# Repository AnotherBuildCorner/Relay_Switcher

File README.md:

# Relay_Switcher
DIY Relay bypass switcher for audio applications

Are you a Guitarist/Bassist?  Do you have a pedalboard that just keeps on getting more complicated?

Worried about losing the high end to the long capactive runs and buffers?

Or maybe you want the ability to control your Star-Trek level board from a small controller on your desk?

Or maybe you looked at the avaliable products, and practically fell out of your chair with the price tag?

Then look no further! In this project you'll find a modular capable, mono or stereo loop bypass switcher with wireless control capability.

## Notes:
V3 Jackless Is up and running in the same 6 back stacked form factor as V2. At this point I believe this represents the final version for this current system based on the WROOM32E. Why?
- After designing this board, I became aware of smaller form factor ESP32's such as the XIAO C6 platform, which is roughly the size of a US Quarter, and has enough GPIO pins to support at least 6 relays.
- These smaller implementations also appear to handle the mesh network past 4 nodes. In the past, while possible, implementing past 4 nodes required additional edits deep in the IDE that I was unable to implement at the time.
- With these smaller nodes, I may be able to use one C6 to control a 6 to 8 loop package box. Incorporated directly into the loop box. Meaning the only wires needed will be Power, and audio. No more RJ45 signal control wire.
- Further, with the practical limitiations of how many nodes are available lifted. The use of C6 nodes means the modularity is further improved to the point of having a control box behind the amp for example, in an effects loop configuration, and one or two on the main pedalboard.  Or even separate pedalboards for different uses.  Or different layers of a rack. The possibilites are endless.
- With a couple small onboard changes, power may even be supplied by the onboard USB connector. Which on it's face doesn't seem that helpful in a 9V power dominated space. However, commercial 5V to 9V power adapters are readily available, which means an entire system could be run from USB power, and by extension, the widely available USB power packs on the market. Why Boost the voltage, just to regulate back to 5V when the supply can be run on pure 5V?

V2 Jackless is up and running in a 6 bay stacked model. In the process a handful of lessons were picked up.
- One, for the jackless model a V3 utilizing probably 3 loops on a single panel with built in signal traces, and possibly breakaway functionality is likely. Attempting to wire the board interconnects resulted in a bit of a mess, one I'm not entirely happy with.
- Two, The original implementations use a completely separate power/control and signal path, not even the grounds are linked. This appears to be an error, and a future revision may include a solderable ground linking pad. In testing this linkage reduced the noise to virtually 0
- Three, the breakout board, while universal has a quirk. When used with the current V2 coms board, Power and ground on the 8 pins are not next to one another. Careful: This may fry some boards.
- Four, some of the pins used on the ESP-32 were linked to serial output, so when those pins are active, the serial monitor and control are disabled. 
## PCB's
### Main Driver Board
### V3
The V3 Design implements some of the noted design problems from V2. Development has continued exclusively with the 3.5mm pitch model. As these are the parts I have on hand. and increasing the terminal block size appears to have little practical benefit.

 Instead of utilizing individual loop boards, there are now a pair of boards linked by a ribbon cable. As a set, these combined boards can support either 6 mono/stereo loops, or 5 mono/stero loops and a mono input selector depending on relay configuration.

 Input Board

 Output Board

This change produces a couple of benefits. First is wiring is vastly improved. with the total wire soldering point count down from 7 per board ( L/R in, L/R out, Ground 9V, and Control signal.) Times 6 loop packages, for a total of 42 solder points. To 16 solder points total for the entire package. As well as being inline, ideal for a ribbon cable, as opposed to scattered across the board.

Additionally, the number of Voltage regulators is down from one per package, to one per PCB (with 3 loops on each). so a 66% reduction overall.

The mentioned power and signal ground linking has been added, provided by the G_link pads located on each PCB, in practice using booth may create a ground loop, so ideally soldering just one is reccomended.

Now the one loss from such a design (albeit minimal in practical usage) is the loops can no longer be order changed by moving around connectors inside the package (or perhaps in the future a complex multi relay network).  In practice this just means physically changing the order of the connected devices at the device instead, and is a minimal downside.

Both Boards Populated

Complete Stacked model Assembly

### V2

V2 makes some significant improvements over the V1 design. And introduces a second design.
the changes are as follows
- Length of board reduced to 61mm Long
- Reduced count of 2n7000 MOSFET drivers from 3 to 1
- Tied status LED directly to the control output for a net -1 2n7000
- Tied the two relay coils together, controlled by single 2n7000

  Among the boards are now the standard stereo jack model, and a pair of new "jackless" models
  The jackless models utilize either a 4x3.5mm pitch or 4x5mm pitch screw terminal block on the IO. this reduces the cost per loop by up $10 in full implementation
  Additionally, it appears the space consumption overall will be significantly reduced with the new design

  The reduced board size should enable either the w/ jack or jackless versions to fit inside a standard 1032L Aluminium looper case
  In testing, the relay coils consume 30mA each, well under the 2n7000's maximum 200mA current.
  the new status LED position can also function as a pulldown for the inputs, reduces the 2n7000 count. And the originals had some current leakage which caused the led to be partially illuminated all the time

### V1

Pictured above is the main relay board. The core Arcitecture is one 5V coil DPDT Relay per signal channel. So for stereo configurations, two relays are required.
Each Relay is driven by a MOSFET 2n7000 switch circuit. As well as the status LED. All three MOSFET gates are tied to a common signal pin, and configured for 3.3V logic.

Each board is also equipped with a 74L05 5V regulator to drop the incoming 9V power, and provide supply for the relay switching.

Each board also has dual power connectors, as well as 3 pin 2.54mm spaced pins for the signal  this alows for easy connections between multiple boards in series.

Finally, the boards are set up to accept switched 1/4 inch stereo jacks. With the switches internally connected, so loops without connections pass signal in either active or inactive state.

(Add PCB wire photos here)

Of further note, was the consideration to keep audio, and control/ power wires as far away, and with minimal crossing as possible. This is to reduce crosstalk from the processor and power supplies into the audio path.

Future iterations will focus on compressing the PCB into a space suitable for a 16L Aluminium looper enclosure. Or possibly a design set up to directly connect to the mono/stereo signal wires, therby reducing the need for the 1/4 Barrel connectors, and reducing the required 1/4 Plugs by 1/2.  This also helps with space considerations.  Considering these plugs cost upwards of $4 each, cutting in half is most welcome, although this reduces how universal this device will be.

### Processor Board
### V2

Changes from V1 to V2 are a different footprint ESP32.  now the Wroom 32E is the standard, with 38 pins avaiable.
The individual pin headers have been replaced by 3x rj45 connectors. each is configured with 6 individual GPIO pins, as well as a 9V connection, and ground.
Additionally, a new breakout board for the rj45 on the receiver end has been created.

### V1

The microprocessor controlling the relays is an ESP32 Devkit C V3 Chosen for it's relative availability, low price, access to Arduino IDE code, and most importantly the dedicated ESP_NOW wireless communication protocol, which will be used to communicate between boards.
This is a relatively simple IO board for connecting to the GPIO of the processor board. The only extra element is another 74L05 voltage regulator connected to the 5V input of the dev board and the 4 pullup resistors slotted in on GPIO pins which only provide input (not suitable for the relay control, but there are already plenty of pins available for most applications).

One shortcoming, there may not be enough GPIO pins to handle the control switches, status LED's, screen, and rotary encoder(s). But this is all currently under development.

This version has a single easily remedied flaw. I had to create a footprint for the ESP32 used as they were what I had to hand, but appear to no longer be made. Well I flipped a ground and power connection, shorting 3.3V power to ground. For now it's just a matter of cutting the trace.

Future versions will probably switch to using a V4 devkit, or the newer devkits based on the S3 processor for more GPIO, and to retain more current availability. 

### IO Board
### V2

The new V2 board corrects an error in the input switching, resulting in one of the inputs being completely unusable.
Additionally, the board size has been significantly reduced in length. and the IO board direct pinouts have been moved directly under each jack.

### V1

This is very similar to the main relay boards.
The differences are the use of the single relay, the dual LED indicators, and the large electrolytic capacitor on the 9V rail.
The Capacitor is a filtering cap, as most of the 9V power supplies will be switched mode supplies, and noise prone.
The relay is no longer used to enable/disable a loop. but instead is used to switch between two possible inputs/outputs. With the other half of the relay dedicated to controlling the indicator LED's
lastly there are direct pinouts on the back of each 1/4 Barrel connector. Should switching features not be desired, these can be used to link the relay loops directly to an output without extra parts.

## Housings
### Control Housing 

### Relay housing V2 
JAckless model.

The latest relay switch is setup to accept 5 of the jackless relay boards, and one V2 IO board with the RJ45 connection board in front.  however this new model is half the height of V1, and is stackable. By splitting the units into modules of 5, this enables break points for things such as Volume pedals, and always on boosts between loop modules. Additional smaller size stackable modules will likely be produced in the future. No one single module can exceed more than 6 relay modules due to the RJ45 connection's configuration.

### Relay housing V1
(picure)
The current housing design uses horizontally stacked relay loops, with a total count of 10. Plus the input and output boards. The IO is located on the front for accesibility, with the loops located on the back.

### Control Housing
(picture
The current design is a single print, 6 switch control with provisions to add a 128X64 OLED.
At present this is in it's early stages, so no provisions to mount the control board, or a larger screen have been included. This will come around in V2  The footswitches are spaced to allow foot, or hand use currently. And the board can be purely powered from a 5V usb supply though the ESP32 board.

## Code
(Coming Soon...)

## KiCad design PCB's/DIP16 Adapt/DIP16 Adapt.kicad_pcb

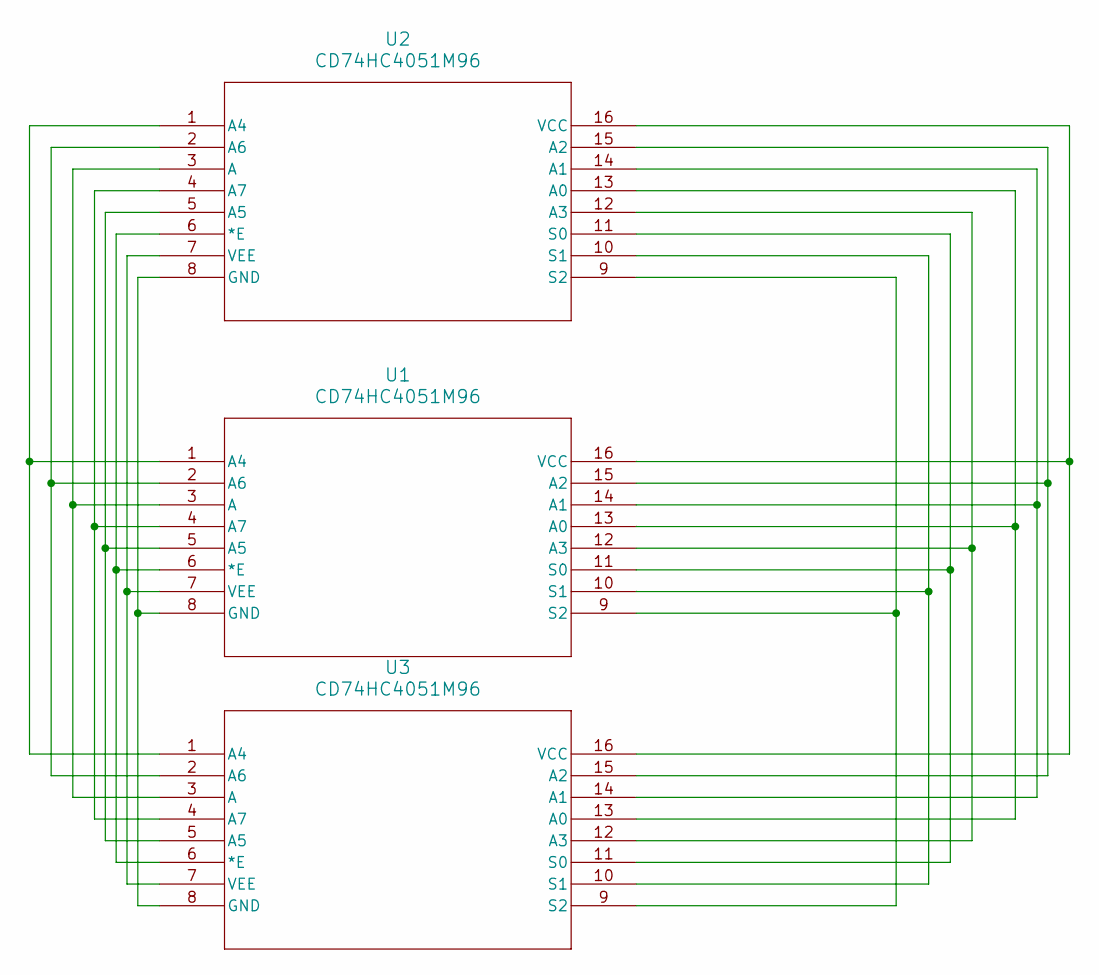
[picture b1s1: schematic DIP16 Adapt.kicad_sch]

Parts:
U1: CD74HC4051M96; DIP-16_W7.62mm_LongPads
U2: CD74HC4051M96; D16
U3: CD74HC4051M96; PW16

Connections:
unnamed: U1.6 (*E), U2.6 (*E), U3.6 (*E)
unnamed: U1.13 (A0), U2.13 (A0), U3.13 (A0)
unnamed: U1.14 (A1), U2.14 (A1), U3.14 (A1)
unnamed: U1.15 (A2), U2.15 (A2), U3.15 (A2)
unnamed: U1.12 (A3), U2.12 (A3), U3.12 (A3)
unnamed: U1.1 (A4), U2.1 (A4), U3.1 (A4)
unnamed: U1.5 (A5), U2.5 (A5), U3.5 (A5)
unnamed: U1.2 (A6), U2.2 (A6), U3.2 (A6)
unnamed: U1.4 (A7), U2.4 (A7), U3.4 (A7)
unnamed: U1.3 (A), U2.3 (A), U3.3 (A)
unnamed: U1.8 (GND), U2.8 (GND), U3.8 (GND)
unnamed: U1.11 (S0), U2.11 (S0), U3.11 (S0)
unnamed: U1.10 (S1), U2.10 (S1), U3.10 (S1)
unnamed: U1.9 (S2), U2.9 (S2), U3.9 (S2)
unnamed: U1.16 (VCC), U2.16 (VCC), U3.16 (VCC)
unnamed: U1.7 (VEE), U2.7 (VEE), U3.7 (VEE)

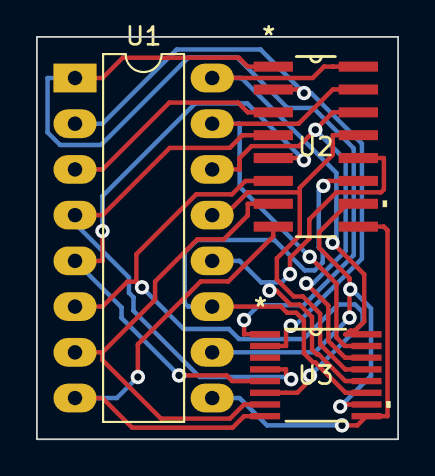
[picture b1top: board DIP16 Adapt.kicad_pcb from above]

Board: 2 copper layers, 20.1 x 22.4 mm, 3 parts (0 on the bottom side), 16 nets.

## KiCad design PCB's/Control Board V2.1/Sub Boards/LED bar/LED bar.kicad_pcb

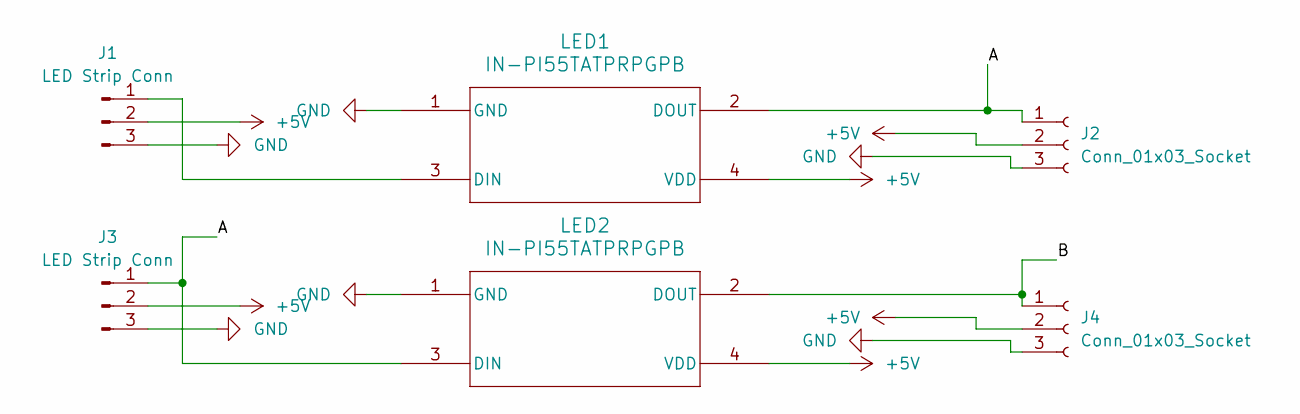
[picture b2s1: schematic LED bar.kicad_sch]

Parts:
J1, J3: LED Strip Conn; PinHeader_1x03_P2.54mm_Vertical
J2, J4: Conn_01x03_Socket; PinHeader_1x03_P2.54mm_Vertical
LED1, LED2: IN-PI55TATPRPGPB; LED_IN-PI55TAT_INL

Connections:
+5V: J1.2, J2.2, J3.2, J4.2, LED1.4 (VDD), LED2.4 (VDD)
/A: J2.1, J3.1, LED1.2 (DOUT), LED2.3 (DIN)
/B: J4.1, LED2.2 (DOUT)
GND: J1.3, J2.3, J3.3, J4.3, LED1.1 (GND), LED2.1 (GND)
unnamed: J1.1, LED1.3 (DIN)

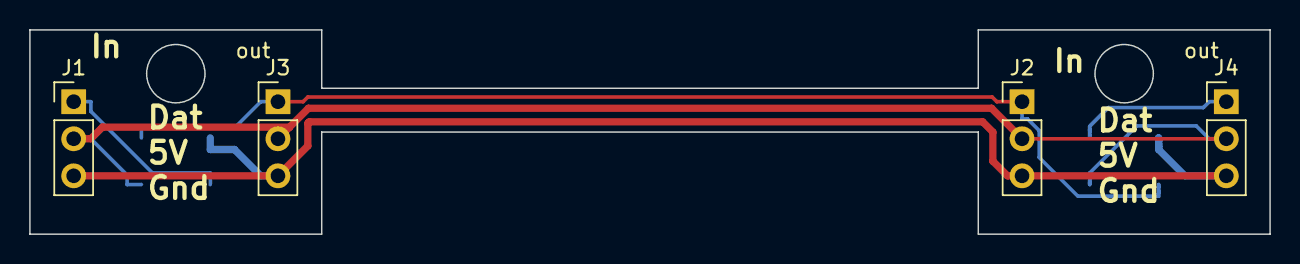
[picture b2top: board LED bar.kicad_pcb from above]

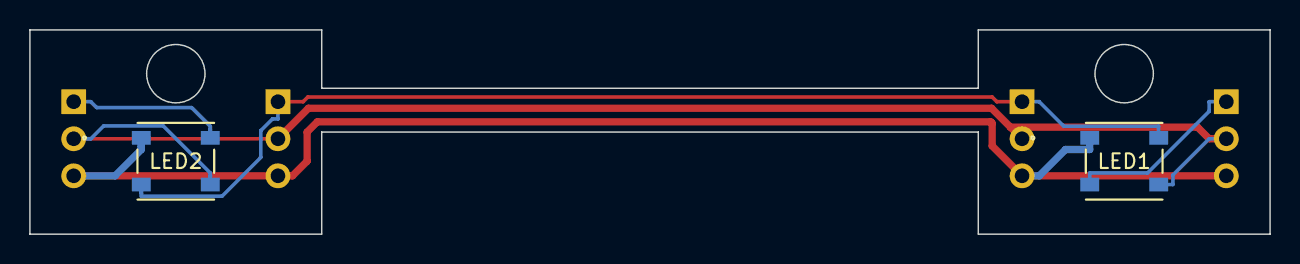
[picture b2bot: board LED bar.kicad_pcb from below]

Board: 2 copper layers, 85.0 x 14.0 mm, 6 parts (2 on the bottom side), 5 nets.

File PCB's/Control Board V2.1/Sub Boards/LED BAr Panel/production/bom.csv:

Designator,Footprint,Quantity,Value,LCSC Part #
"J1_5, J1_4, J1_3, J1_2, J1, J3_5, J3_4, J3_3, J3_2, J3",PinHeader_1x03_P2.54mm_Vertical,10,LED Strip Conn,
"J2_5, J2_4, J2_3, J2_2, J2, J4_5, J4_4, J4_3, J4_2, J4",PinHeader_1x03_P2.54mm_Vertical,10,Conn_01x03_Socket,
"KiKit_MB_10_1, KiKit_MB_10_2, KiKit_MB_10_3, KiKit_MB_10_4, KiKit_MB_11_1, KiKit_MB_11_2, KiKit_MB_11_3, KiKit_MB_11_4, KiKit_MB_12_1, KiKit_MB_12_2, KiKit_MB_12_3, KiKit_MB_12_4, KiKit_MB_13_1, KiKit_MB_13_2, KiKit_MB_13_3, KiKit_MB_13_4, KiKit_MB_14_1, KiKit_MB_14_2, KiKit_MB_14_3, KiKit_MB_14_4, KiKit_MB_15_1, KiKit_MB_15_2, KiKit_MB_15_3, KiKit_MB_15_4, KiKit_MB_16_1, KiKit_MB_16_2, KiKit_MB_16_3, KiKit_MB_16_4, KiKit_MB_17_1, KiKit_MB_17_2, KiKit_MB_17_3, KiKit_MB_17_4, KiKit_MB_18_1, KiKit_MB_18_2, KiKit_MB_18_3, KiKit_MB_18_4, KiKit_MB_19_1, KiKit_MB_19_2, KiKit_MB_19_3, KiKit_MB_19_4, KiKit_MB_1_1, KiKit_MB_1_2, KiKit_MB_1_3, KiKit_MB_1_4, KiKit_MB_20_1, KiKit_MB_20_2, KiKit_MB_20_3, KiKit_MB_20_4, KiKit_MB_21_1, KiKit_MB_21_2, KiKit_MB_21_3, KiKit_MB_21_4, KiKit_MB_22_1, KiKit_MB_22_2, KiKit_MB_22_3, KiKit_MB_22_4, KiKit_MB_23_1, KiKit_MB_23_2, KiKit_MB_23_3, KiKit_MB_23_4, KiKit_MB_24_1, KiKit_MB_24_2, KiKit_MB_24_3, KiKit_MB_24_4, KiKit_MB_25_1, KiKit_MB_25_2, KiKit_MB_25_3, KiKit_MB_25_4, KiKit_MB_26_1, KiKit_MB_26_2, KiKit_MB_26_3, KiKit_MB_26_4, KiKit_MB_27_1, KiKit_MB_27_2, KiKit_MB_27_3, KiKit_MB_27_4, KiKit_MB_28_1, KiKit_MB_28_2, KiKit_MB_28_3, KiKit_MB_28_4, KiKit_MB_29_1, KiKit_MB_29_2, KiKit_MB_29_3, KiKit_MB_29_4, KiKit_MB_2_1, KiKit_MB_2_2, KiKit_MB_2_3, KiKit_MB_2_4, KiKit_MB_30_1, KiKit_MB_30_2, KiKit_MB_30_3, KiKit_MB_30_4, KiKit_MB_31_1, KiKit_MB_31_2, KiKit_MB_31_3, KiKit_MB_31_4, KiKit_MB_32_1, KiKit_MB_32_2, KiKit_MB_32_3, KiKit_MB_32_4, KiKit_MB_33_1, KiKit_MB_33_2, KiKit_MB_33_3, KiKit_MB_33_4, KiKit_MB_34_1, KiKit_MB_34_2, KiKit_MB_34_3, KiKit_MB_34_4, KiKit_MB_35_1, KiKit_MB_35_2, KiKit_MB_35_3, KiKit_MB_35_4, KiKit_MB_36_1, KiKit_MB_36_2, KiKit_MB_36_3, KiKit_MB_36_4, KiKit_MB_37_1, KiKit_MB_37_2, KiKit_MB_37_3, KiKit_MB_37_4, KiKit_MB_38_1, KiKit_MB_38_2, KiKit_MB_38_3, KiKit_MB_38_4, KiKit_MB_39_1, KiKit_MB_39_2, KiKit_MB_39_3, KiKit_MB_39_4, KiKit_MB_3_1, KiKit_MB_3_2, KiKit_MB_3_3, KiKit_MB_3_4, KiKit_MB_40_1, KiKit_MB_40_2, KiKit_MB_40_3, KiKit_MB_40_4, KiKit_MB_41_1, KiKit_MB_41_2, KiKit_MB_41_3, KiKit_MB_41_4, KiKit_MB_42_1, KiKit_MB_42_2, KiKit_MB_42_3, KiKit_MB_42_4, KiKit_MB_43_1, KiKit_MB_43_2, KiKit_MB_43_3, KiKit_MB_43_4, KiKit_MB_44_1, KiKit_MB_44_2, KiKit_MB_44_3, KiKit_MB_44_4, KiKit_MB_45_1, KiKit_MB_45_2, KiKit_MB_45_3, KiKit_MB_45_4, KiKit_MB_46_1, KiKit_MB_46_2, KiKit_MB_46_3, KiKit_MB_46_4, KiKit_MB_47_1, KiKit_MB_47_2, KiKit_MB_47_3, KiKit_MB_47_4, KiKit_MB_48_1, KiKit_MB_48_2, KiKit_MB_48_3, KiKit_MB_48_4, KiKit_MB_4_1, KiKit_MB_4_2, KiKit_MB_4_3, KiKit_MB_4_4, KiKit_MB_5_1, KiKit_MB_5_2, KiKit_MB_5_3, KiKit_MB_5_4, KiKit_MB_6_1, KiKit_MB_6_2, KiKit_MB_6_3, KiKit_MB_6_4, KiKit_MB_7_1, KiKit_MB_7_2, KiKit_MB_7_3, KiKit_MB_7_4, KiKit_MB_8_1, KiKit_MB_8_2, KiKit_MB_8_3, KiKit_MB_8_4, KiKit_MB_9_1, KiKit_MB_9_2, KiKit_MB_9_3, KiKit_MB_9_4",NPTH,192,NPTH,
"LED1_5, LED1_4, LED1_3, LED1_2, LED1, LED2_5, LED2_4, LED2_3, LED2_2, LED2",LED_IN-PI55TAT_INL,10,IN-PI55TATPRPGPB,

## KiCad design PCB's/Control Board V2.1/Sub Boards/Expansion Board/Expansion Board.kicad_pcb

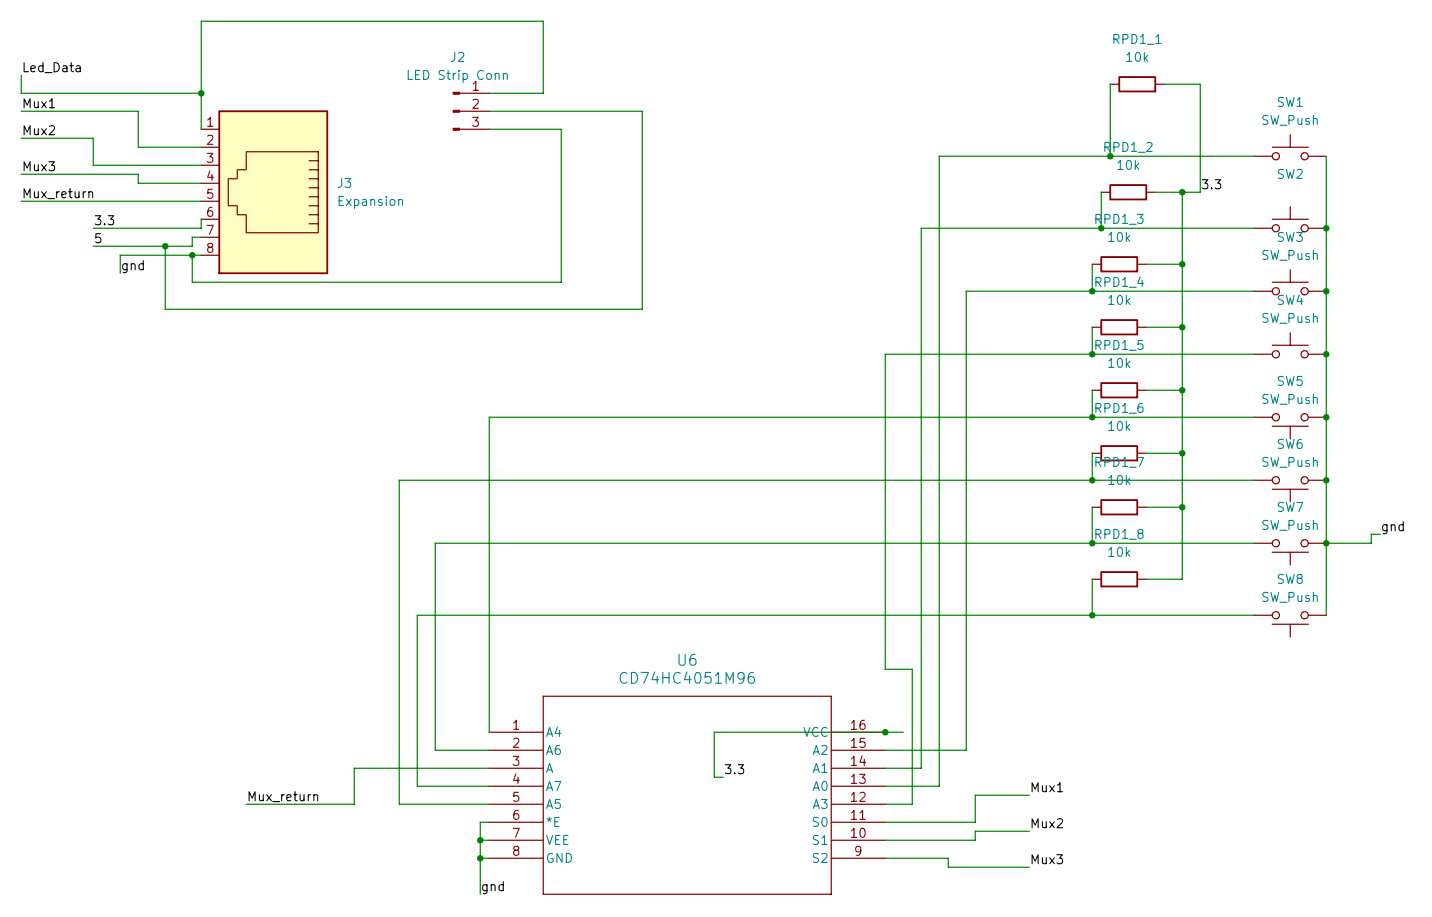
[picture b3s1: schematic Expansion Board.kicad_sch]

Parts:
J2: LED Strip Conn; PinHeader_1x03_P2.54mm_Vertical
J3: Expansion; RJ45_Amphenol_54602-x08_Horizontal
RPD1_1, RPD1_2, RPD1_3, RPD1_4, RPD1_5, RPD1_6, RPD1_7, RPD1_8: 10k; R_0805_2012Metric_Pad1.20x1.40mm_HandSolder
SW1, SW3, SW4, SW5, SW6, SW7, SW8: SW_Push; TerminalBlock_4Ucon_1x02_P3.50mm_Vertical
SW2: TerminalBlock_4Ucon_1x02_P3.50mm_Vertical
U6: CD74HC4051M96; QSOP-16_3.9x4.9mm_P0.635mm

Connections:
/3.3: J3.6, RPD1_1.2, RPD1_2.2, RPD1_3.2, RPD1_4.2, RPD1_5.2, RPD1_6.2, RPD1_7.2, RPD1_8.2, U6.16 (VCC)
/5: J2.2, J3.7
/Led_Data: J2.1, J3.1
/Mux1: J3.2, U6.11 (S0)
/Mux2: J3.3, U6.10 (S1)
/Mux3: J3.4, U6.9 (S2)
/Mux_return: J3.5, U6.3 (A)
/gnd: J2.3, J3.8, SW1.2, SW2.2, SW3.2, SW4.2, SW5.1, SW6.1, SW7.1, SW8.1, U6.6 (*E), U6.7 (VEE), U6.8 (GND)
unnamed: RPD1_1.1, SW1.1, U6.13 (A0)
unnamed: RPD1_2.1, SW2.1, U6.14 (A1)
unnamed: RPD1_3.1, SW3.1, U6.15 (A2)
unnamed: RPD1_4.1, SW4.1, U6.12 (A3)
unnamed: RPD1_5.1, SW5.2, U6.1 (A4)
unnamed: RPD1_6.1, SW6.2, U6.5 (A5)
unnamed: RPD1_7.1, SW7.2, U6.2 (A6)
unnamed: RPD1_8.1, SW8.2, U6.4 (A7)

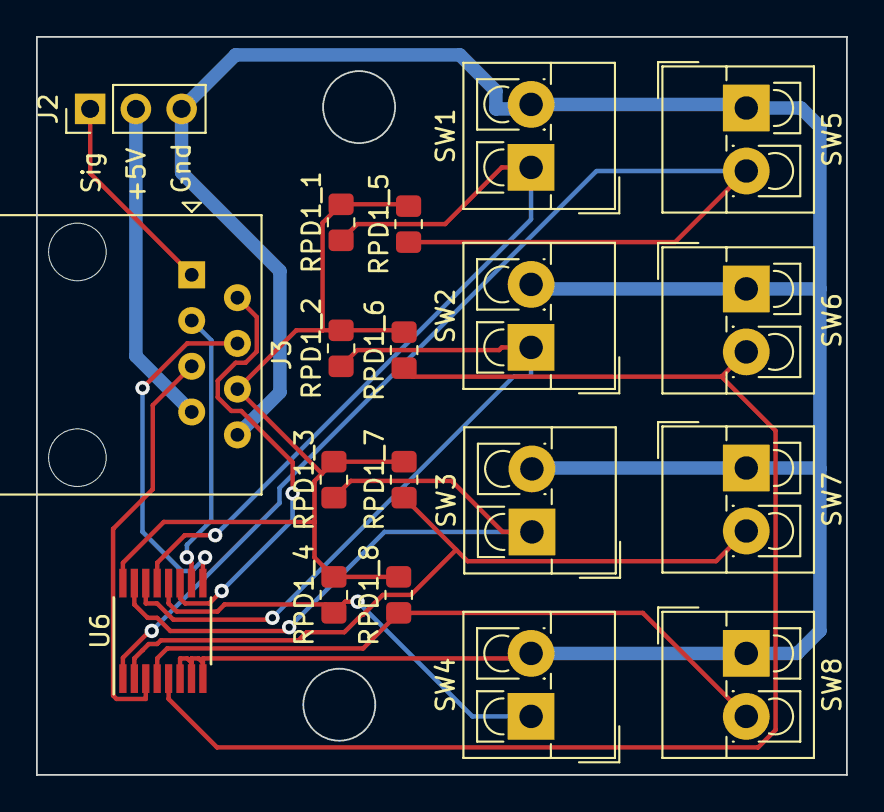
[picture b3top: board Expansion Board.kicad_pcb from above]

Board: 2 copper layers, 45.0 x 41.0 mm, 19 parts (0 on the bottom side), 16 nets.

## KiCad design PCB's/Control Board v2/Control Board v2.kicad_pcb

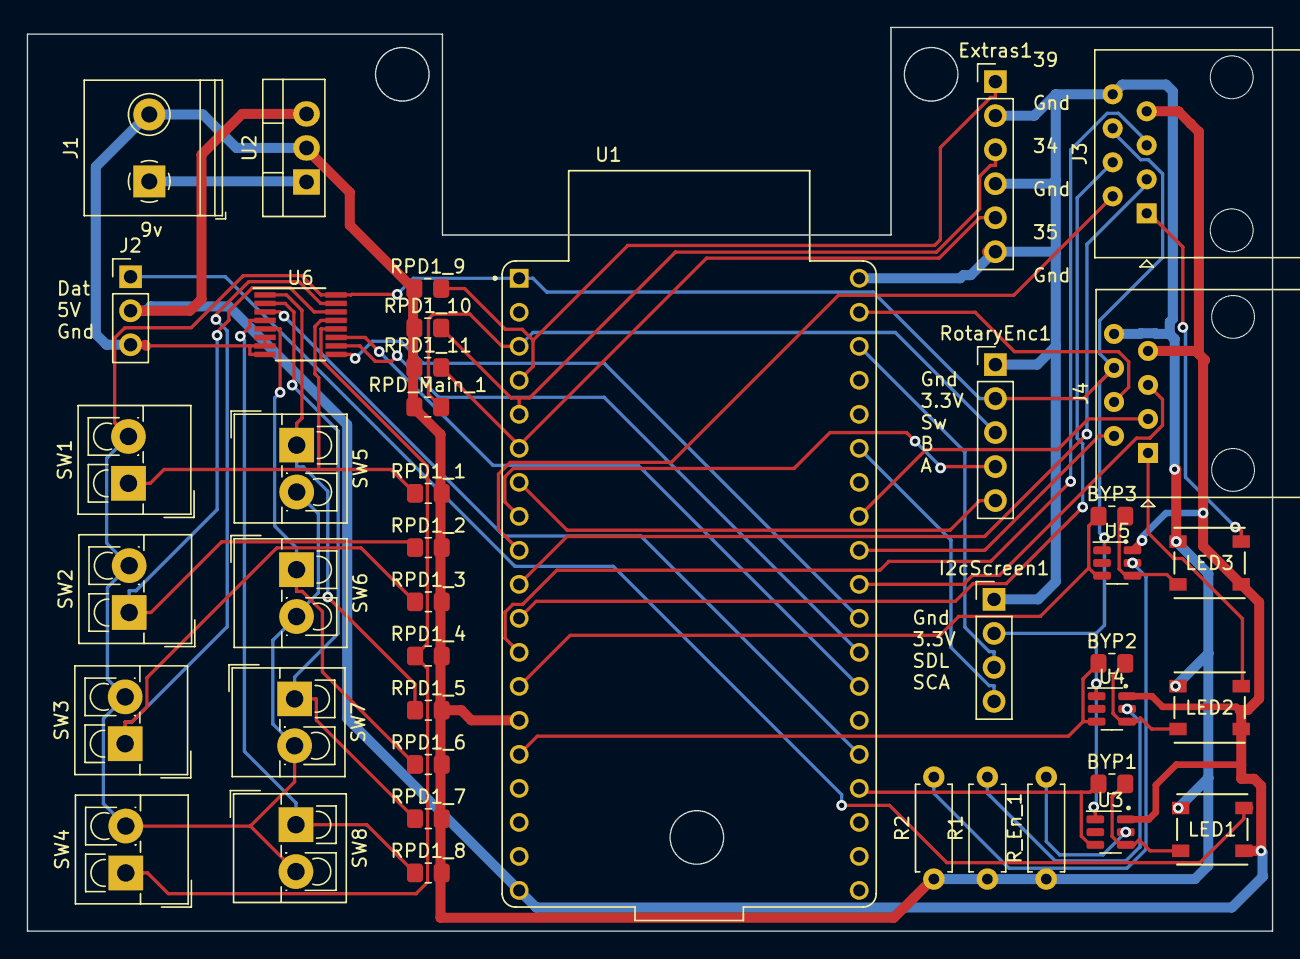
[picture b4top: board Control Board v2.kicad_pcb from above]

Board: 2 copper layers, 93.0 x 67.5 mm, 42 parts (0 on the bottom side), 44 nets.

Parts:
BYP1, BYP2, BYP3: R_0805_2012Metric_Pad1.20x1.40mm_HandSolder
Extras1: Conn_01x06_Pin; PinHeader_1x06_P2.54mm_Vertical
I2cScreen1: Conn_01x05_Pin; PinHeader_1x04_P2.54mm_Vertical
J1: Power In; TerminalBlock_Philmore_TB132_1x02_P5.00mm_Horizontal
J2: LED Strip Conn; PinHeader_1x03_P2.54mm_Vertical
J3, J4: Expansion; RJ45_Amphenol_54602-x08_Horizontal
LED1, LED2, LED3: IN-PI55TATPRPGPB; LED_IN-PI55TAT_INL
R1, R2: R; R_Axial_DIN0207_L6.3mm_D2.5mm_P7.62mm_Horizontal
RPD1_1, RPD1_2, RPD1_3, RPD1_4, RPD1_5, RPD1_6, RPD1_7, RPD1_8, RPD1_9, RPD1_10, RPD1_11: 10k; R_0805_2012Metric_Pad1.20x1.40mm_HandSolder
RPD_Main_1: 10k; R_0805_2012Metric_Pad1.20x1.40mm_HandSolder
R_En_1: R; R_Axial_DIN0207_L6.3mm_D2.5mm_P7.62mm_Horizontal
RotaryEnc1: Conn_01x05_Pin; PinHeader_1x05_P2.54mm_Vertical
SW1, SW2, SW3, SW4, SW5, SW6, SW7, SW8: SW_Push; TerminalBlock_4Ucon_1x02_P3.50mm_Vertical
U1: ESP32-DEVKITC-32E; MODULE_ESP32-DEVKITC-32E
U2: L7805; TO-220-3_Vertical
U3, U4, U5: TXS0101DBV; SOT-23-6
U6: CD74HC4051M96; QSOP-16_3.9x4.9mm_P0.635mm

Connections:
+3.3V: I2cScreen1.2, J3.6, J4.6, RotaryEnc1.2, SW1.2, SW2.2, SW3.2, SW4.2, SW5.2, SW6.2, SW7.2, SW8.2, U1.J2_1 (3V3), U3.1 (V_{CCA}), U4.1 (V_{CCA}), U5.1 (V_{CCA}), U6.16 (VCC)
+5V: J2.2, J3.7, J4.7, LED1.4 (VDD), LED2.4 (VDD), LED3.4 (VDD), U1.J2_19 (EXT_5V), U2.3 (OUT), U3.6 (V_{CCB}), U4.6 (V_{CCB}), U5.6 (V_{CCB})
+9V: J1.1, U2.1 (IN)
/Enc_A: RotaryEnc1.5, U1.J2_7 (IO32)
/Enc_B: RotaryEnc1.4, U1.J2_8 (IO33)
/Enc_Sw: RPD_Main_1.2, RotaryEnc1.3, U1.J2_3 (SENSOR_VP)
/GP34: Extras1.3, RPD1_10.2, U1.J2_5 (IO34)
/GP35: Extras1.5, RPD1_11.2, U1.J2_6 (IO35)
/GP39: Extras1.1, RPD1_9.2, U1.J2_4 (SENSOR_VN)
/I2C_SCL: I2cScreen1.3, U1.J3_3 (IO22)
/I2C_SDA: I2cScreen1.4, U1.J3_6 (IO21)
/Mux2_1: J4.2, U1.J3_9 (IO18)
/Mux2_2: J4.3, U1.J3_8 (IO19)
/Mux2_3: J4.4, U1.J3_2 (IO23)
/Mux2_return: J4.5, U1.J3_10 (IO5)
/Mux3_1: J3.2, U1.J2_9 (IO25)
/Mux3_2: J3.3, U1.J2_10 (IO26)
/Mux3_3: J3.4, U1.J2_11 (IO27)
/Mux3_return: J3.5, U1.J2_12 (IO14)
GND: Extras1.2, Extras1.4, Extras1.6, I2cScreen1.1, J1.2, J2.3, J3.8, J4.8, LED1.1 (GND), LED2.1 (GND), LED3.1 (GND), R1.1, R2.1, RPD1_1.2, RPD1_2.2, RPD1_3.2, RPD1_4.2, RPD1_5.2, RPD1_6.2, RPD1_7.2, RPD1_8.2, RPD1_9.1, RPD1_10.1, RPD1_11.1, RPD_Main_1.1, R_En_1.1, RotaryEnc1.1, U1.J2_14 (GND_J2_14), U1.J3_1 (GND_J3_1), U2.2 (GND), U6.6 (*E), U6.7 (VEE), U6.8 (GND)
LED_1_Data: J2.1, LED1.2 (DOUT)
LED_1_sig: BYP1.1, U1.J3_16 (IO15), U3.3 (A)
LED_2_Data: J4.1, LED2.2 (DOUT)
LED_2_sig: BYP2.1, U1.J2_15 (IO13), U4.3 (A)
LED_3_Data: J3.1, LED3.2 (DOUT)
LED_3_sig: BYP3.1, U1.J2_13 (IO12), U5.3 (A)
Mux1_1: U1.J3_13 (IO4), U6.11 (S0)
Mux1_2: U1.J3_12 (IO16), U6.10 (S1)
Mux1_3: U1.J3_11 (IO17), U6.9 (S2)
Mux1_return: U1.J3_15 (IO2), U6.3 (A)
unnamed: BYP1.2, LED1.3 (DIN), U3.4 (B)
unnamed: BYP2.2, LED2.3 (DIN), U4.4 (B)
unnamed: BYP3.2, LED3.3 (DIN), U5.4 (B)
unnamed: R_En_1.2, U3.5 (OE)
unnamed: R1.2, U4.5 (OE)
unnamed: R2.2, U5.5 (OE)
unnamed: RPD1_1.1, SW1.1, U6.13 (A0)
unnamed: RPD1_2.1, SW2.1, U6.14 (A1)
unnamed: RPD1_3.1, SW3.1, U6.15 (A2)
unnamed: RPD1_4.1, SW4.1, U6.12 (A3)
unnamed: RPD1_5.1, SW5.1, U6.1 (A4)
unnamed: RPD1_6.1, SW6.1, U6.5 (A5)
unnamed: RPD1_7.1, SW7.1, U6.2 (A6)
unnamed: RPD1_8.1, SW8.1, U6.4 (A7)

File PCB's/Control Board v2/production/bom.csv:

Designator,Footprint,Quantity,Value,LCSC Part #
"BYP1, BYP2, BYP3",0805,3,~,
Extras1,PinHeader_1x06_P2.54mm_Vertical,1,Conn_01x06_Pin,
I2cScreen1,PinHeader_1x04_P2.54mm_Vertical,1,Conn_01x05_Pin,
J1,TerminalBlock_Philmore_TB132_1x02_P5.00mm_Horizontal,1,Power In,
J2,PinHeader_1x03_P2.54mm_Vertical,1,LED Strip Conn,
"J3, J4",RJ45_Amphenol_54602-x08_Horizontal,2,Expansion,
"LED1, LED2, LED3",LED_IN-PI55TAT_INL,3,IN-PI55TATPRPGPB,
"R1, R2, R_En_1",R_Axial_DIN0207_L6.3mm_D2.5mm_P7.62mm_Horizontal,3,R,
"RPD1_1, RPD1_10, RPD1_11, RPD1_2, RPD1_3, RPD1_4, RPD1_5, RPD1_6, RPD1_7, RPD1_8, RPD1_9, RPD_Main_1",0805,12,10k,
RotaryEnc1,PinHeader_1x05_P2.54mm_Vertical,1,Conn_01x05_Pin,
"SW1, SW2, SW3, SW4, SW5, SW6, SW7, SW8",TerminalBlock_4Ucon_1x02_P3.50mm_Vertical,8,SW_Push,
U1,MODULE_ESP32-DEVKITC-32E,1,ESP32-DEVKITC-32E,
U2,TO-220-3_Vertical,1,L7805,
"U3, U4, U5",SOT-23-6,3,TXS0101DBV,
U6,QSOP-16_3.9x4.9mm_P0.635mm,1,CD74HC4051M96,

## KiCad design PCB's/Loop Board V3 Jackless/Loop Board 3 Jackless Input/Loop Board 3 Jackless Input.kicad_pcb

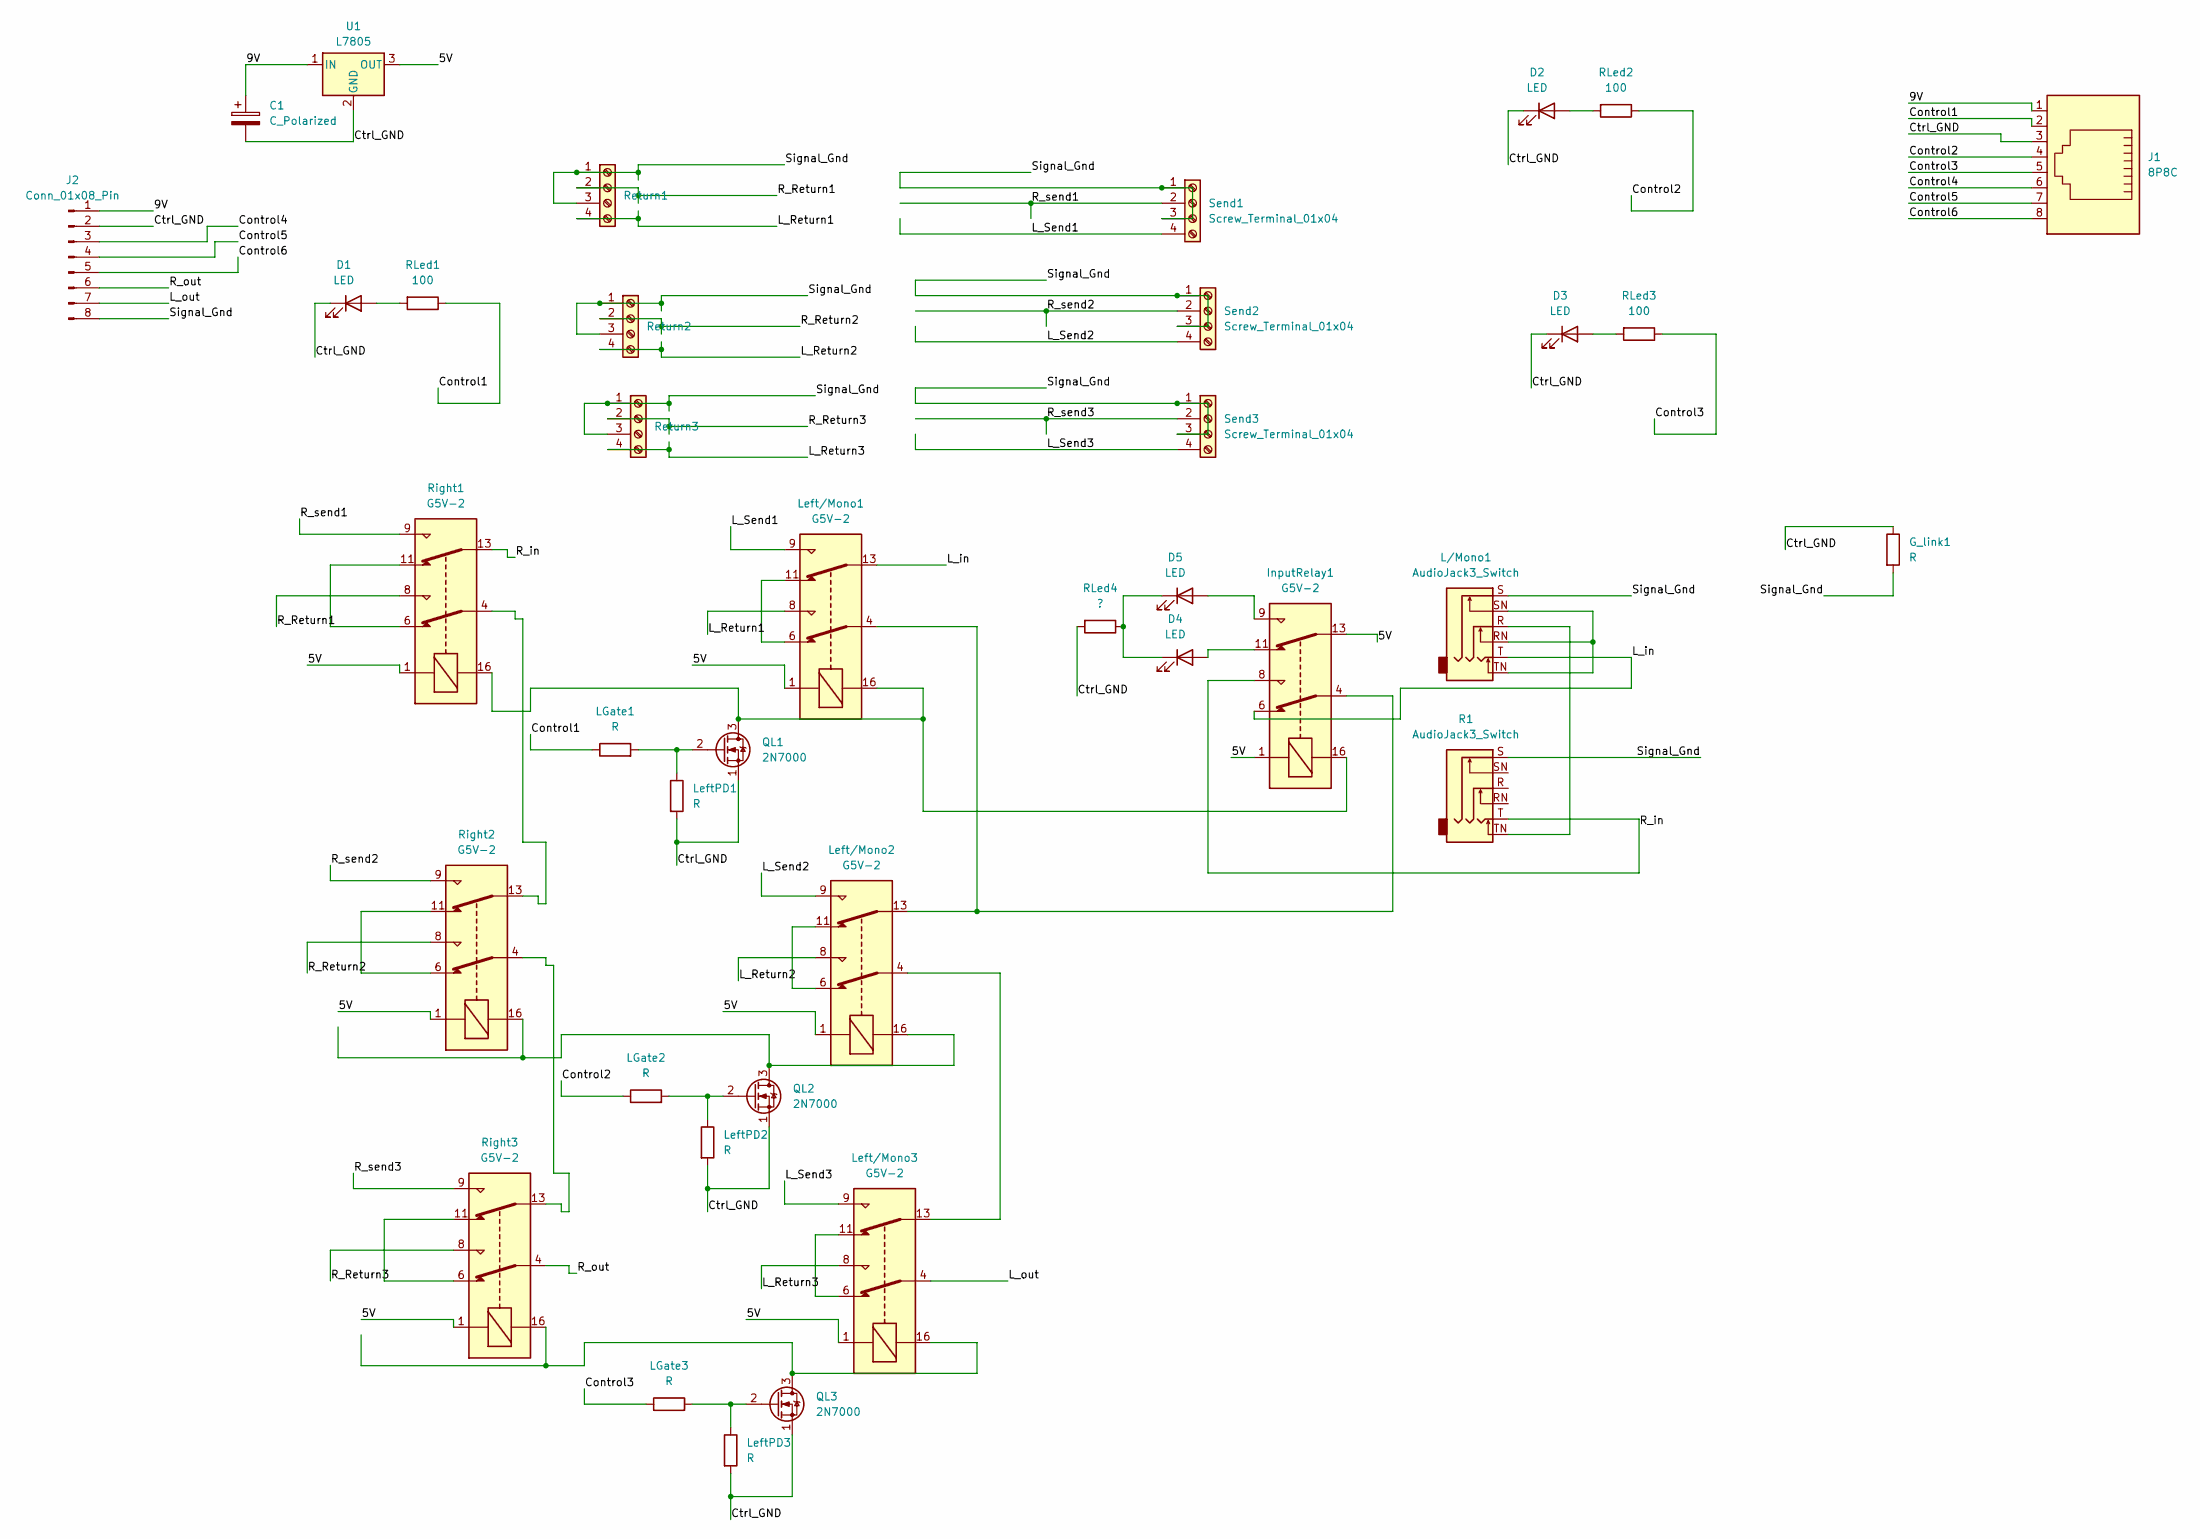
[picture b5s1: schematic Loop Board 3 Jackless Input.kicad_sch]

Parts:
C1: C_Polarized; CP_Radial_D10.0mm_P3.50mm
D1, D2, D3, D4, D5: LED; LED_D5.0mm
G_link1: R; R_0805_2012Metric
InputRelay1: G5V-2; Relay_DPDT_Omron_G5V-2
J1: 8P8C; RJ45_Amphenol_54602-x08_Horizontal
J2: Conn_01x08_Pin; PinSocket_1x08_P2.54mm_Vertical
L/Mono1: AudioJack3_Switch; Jack_6.35mm_Neutrik_NMJ6HCD2_Horizontal
LGate1, LGate2, LGate3: R; R_Axial_DIN0207_L6.3mm_D2.5mm_P7.62mm_Horizontal
Left/Mono1, Left/Mono2, Left/Mono3: G5V-2; Relay_DPDT_Omron_G5V-2
LeftPD1, LeftPD2, LeftPD3: R; R_Axial_DIN0207_L6.3mm_D2.5mm_P7.62mm_Horizontal
QL1, QL2, QL3: 2N7000; TO-92_Inline
R1: AudioJack3_Switch; Jack_6.35mm_Neutrik_NMJ6HCD2_Horizontal
RLed1, RLed2, RLed3: 100; R_Axial_DIN0207_L6.3mm_D2.5mm_P7.62mm_Horizontal
RLed4: ?; R_Axial_DIN0207_L6.3mm_D2.5mm_P7.62mm_Horizontal
Return1, Return2, Return3: Screw_Terminal_01x04; CUI_TB001-500-04BE
Right1, Right2, Right3: G5V-2; Relay_DPDT_Omron_G5V-2
Send1, Send2, Send3: Screw_Terminal_01x04; CUI_TB001-500-04BE
U1: L7805; TO-220-3_Vertical

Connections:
/5V: InputRelay1.1, InputRelay1.13, Left/Mono1.1, Left/Mono2.1, Left/Mono3.1, Right1.1, Right2.1, Right3.1, U1.3 (OUT)
/9V: C1.1, J1.1, J2.1, U1.1 (IN)
/Control1: J1.2, LGate1.1, RLed1.1
/Control2: J1.4, LGate2.1, RLed2.1
/Control3: J1.5, LGate3.1, RLed3.1
/Control4: J1.6, J2.3
/Control5: J1.7, J2.4
/Control6: J1.8, J2.5
/Ctrl_GND: C1.2, D1.1 (K), D2.1 (K), D3.1 (K), G_link1.1, J1.3, J2.2, LeftPD1.2, LeftPD2.2, LeftPD3.2, QL1.1 (S), QL2.1 (S), QL3.1 (S), RLed4.2, U1.2 (GND)
/L_Return1: Left/Mono1.8, Return1.4
/L_Return2: Left/Mono2.8, Return2.4
/L_Return3: Left/Mono3.8, Return3.4
/L_Send1: Left/Mono1.9, Send1.4
/L_Send2: Left/Mono2.9, Send2.4
/L_Send3: Left/Mono3.9, Send3.4
/L_in: InputRelay1.6, L/Mono1.T, Left/Mono1.13
/L_out: J2.7, Left/Mono3.4
/R_Return1: Return1.2, Right1.8
/R_Return2: Return2.2, Right2.8
/R_Return3: Return3.2, Right3.8
/R_in: InputRelay1.8, R1.T, Right1.13
/R_out: J2.6, Right3.4
/R_send1: Right1.9, Send1.2
/R_send2: Right2.9, Send2.2
/R_send3: Right3.9, Send3.2
/Signal_Gnd: G_link1.2, J2.8, L/Mono1.S, R1.S, Return1.1, Return1.3, Return2.1, Return2.3, Return3.1, Return3.3, Send1.1, Send1.3, Send2.1, Send2.3, Send3.1, Send3.3
unnamed: D1.2 (A), RLed1.2
unnamed: D2.2 (A), RLed2.2
unnamed: D3.2 (A), RLed3.2
unnamed: D4.2 (A), InputRelay1.11
unnamed: D4.1 (K), D5.1 (K), RLed4.1
unnamed: D5.2 (A), InputRelay1.9
unnamed: InputRelay1.4, Left/Mono1.4, Left/Mono2.13
unnamed: L/Mono1.R, R1.TN
unnamed: L/Mono1.RN, L/Mono1.SN, L/Mono1.TN
unnamed: Left/Mono1.6, Left/Mono1.11
unnamed: Left/Mono2.4, Left/Mono3.13
unnamed: Left/Mono2.6, Left/Mono2.11
unnamed: Left/Mono3.6, Left/Mono3.11
unnamed: InputRelay1.16, Left/Mono1.16, QL1.3 (D), Right1.16
unnamed: LGate1.2, LeftPD1.1, QL1.2 (G)
unnamed: Left/Mono2.16, QL2.3 (D), Right2.16
unnamed: LGate2.2, LeftPD2.1, QL2.2 (G)
unnamed: Left/Mono3.16, QL3.3 (D), Right3.16
unnamed: LGate3.2, LeftPD3.1, QL3.2 (G)
unnamed: Right1.4, Right2.13
unnamed: Right1.6, Right1.11
unnamed: Right2.4, Right3.13
unnamed: Right2.6, Right2.11
unnamed: Right3.6, Right3.11

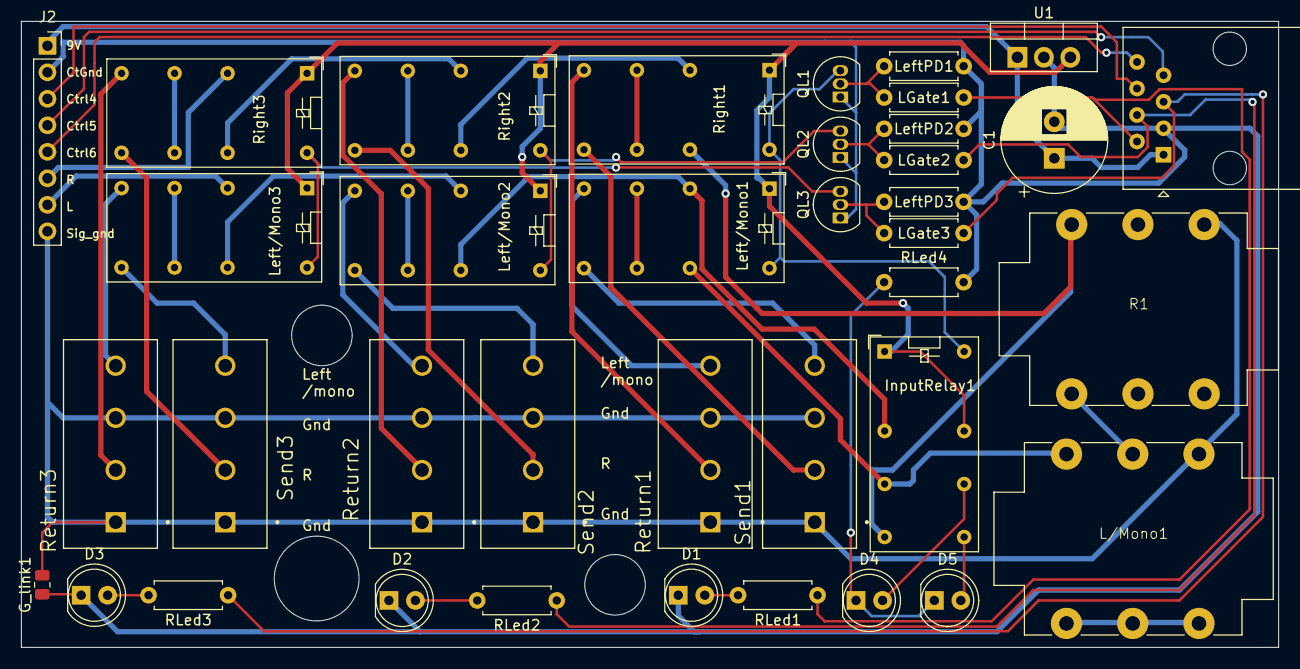
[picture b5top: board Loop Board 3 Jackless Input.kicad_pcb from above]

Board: 2 copper layers, 120.5 x 60.0 mm, 38 parts (0 on the bottom side), 50 nets.
